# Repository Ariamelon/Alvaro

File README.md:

# Alvaro
 Pro Micro-compatible 32u4 Breakout Board

## Disclaimer
This board is a heavily-modified [Goldfish Rev. C](https://github.com/staticintlucas/Goldfish). While the schematic, basic layout, pinout (of course) etc is essentially the same, it uses 0603 components instead of 0402 and has some other changes.

## Key Features
* Mid-mount USB-C connector using a low-profile USB C 2.0 connector.
* Pin-compatible with the original Pro Micro.
* 5 extra pins on the bottom like the Elite-C and Goldfish.
* Exposed USB data lines on 2.54mm grid.
* Easier to solder than the Goldfish.
* Has fuse unlike Goldfish.
* On-board power LED.
* Fully hand-solderable.

## Changelog
* 27/09/2020: Initial commit.
* 29/09/2020: Switched D1 size from SOD323 to SOD123.
* 13/10/2020: Updated to V1.1. Added F1 1206 500mA polyfuse.
* 17/10/2020: Updated to V1.2. Moved location of parts closer to center.
* 31/10/2020: Updated to V1.3. Added 0603 power indicator LED, changed R6 from 10k to 1k LED resistor.
* 29/11/2020: Updated to V1.4. Increased size of 3225 crystal pads, changed USB C THT holes back to single oval shape, added THT pad under 32u4 to allow for the entire thing to be hand-soldered easier.
* 3/12/2020: Updated to V1.5. Decreased size of 3225 crystal pads again and changed them to THT. Staggered components to allow for easier soldering.

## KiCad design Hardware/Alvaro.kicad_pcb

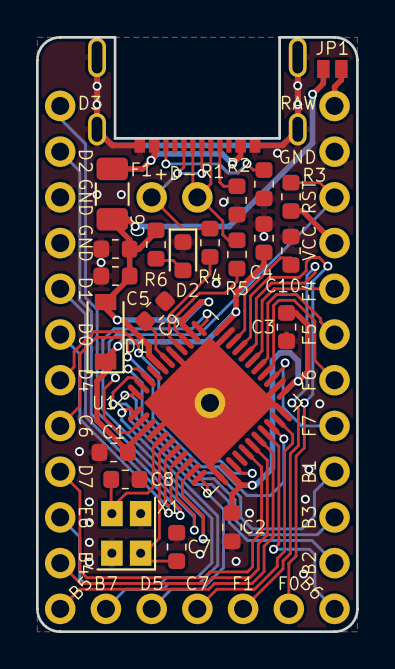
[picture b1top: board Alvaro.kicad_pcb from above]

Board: 2 copper layers, 17.8 x 33.0 mm, 27 parts (0 on the bottom side), 40 nets.

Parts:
C1, C2, C3, C4, C5, C10: 0u1; C_0603_1608Metric
C6: 4u7; C_0603_1608Metric
C7, C8: 22p; C_0603_1608Metric
C9: 1u; C_0603_1608Metric
D1: D_Schottky; D_SOD-123
D2: LED; LED_0603_1608Metric
F1: Polyfuse_Small; Fuse_1206_3216Metric
J2: 01x02; Pins2
J3, J4: 01x12; Pins12
J5: 01x05; Pins5
JP1: RAW; SolderJumper-2_P1.3mm_Open_Pad1.0x1.5mm
P1: USB_C_Receptacle_USB2.0; USB-C-C168688
R1, R2: 5k1; R_0603_1608Metric
R3: 10k; R_0603_1608Metric
R4, R5: 22; R_0603_1608Metric
R6: 1k; R_0603_1608Metric
U1: ATmega32U4; QFN-44-1EP_7x7mm_P0.5mm_EP5.2x5.2mm
X1: 16MHz; Crystal_SMD_SeikoEpson_FA238-4Pin_3.2x2.5mm

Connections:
/D+: J2.1, P1.A6, P1.B6, R4.2
/D-: J2.2, P1.A7, P1.B7, R5.2
/PB1: J3.9, U1.9
/PB2: J3.11, U1.10
/PB3: J3.10, U1.11
/PB4: J4.2, U1.28
/PB5: J4.1, U1.29
/PB6: J3.12, U1.30
/PB7: J5.5, U1.12
/PC6: J4.5, U1.31
/PC7: J5.3, U1.32
/PD0: J4.7, U1.18
/PD1: J4.8, U1.19
/PD2: J4.11, U1.20
/PD3: J4.12, U1.21
/PD4: J4.6, U1.25
/PD5: J5.4, U1.22
/PD7: J4.4, U1.27
/PE6: J4.3, U1.1
/PF0: J5.1, U1.41
/PF1: J5.2, U1.40
/PF4: J3.5, U1.39
/PF5: J3.6, U1.38
/PF6: J3.7, U1.37
/PF7: J3.8, U1.36
/RESET: J3.3, R3.1, U1.13
GND: C1.2, C2.2, C3.2, C4.2, C5.2, C6.2, C7.2, C8.2, C9.2, C10.2, D2.1, J3.2, J4.9, J4.10, P1.A1, P1.S1, R1.1, R2.1, U1.5, U1.15, U1.23, U1.33, U1.35, U1.43, U1.45, X1.2, X1.4
unnamed: C7.1, U1.17, X1.1
unnamed: C8.1, U1.16, X1.3
unnamed: C9.1, U1.6
unnamed: C10.1, U1.42
unnamed: D2.2, R6.1
unnamed: F1.2, P1.A4
unnamed: J3.1, JP1.2
unnamed: P1.A5, R1.2
unnamed: P1.B5, R2.2
unnamed: R4.1, U1.4
unnamed: R5.1, U1.3
VBUS: C5.1, C6.1, D1.2, F1.1, JP1.1, R6.2, U1.2, U1.7
VCC: C1.1, C2.1, C3.1, C4.1, D1.1, J3.4, R3.2, U1.14, U1.24, U1.34, U1.44

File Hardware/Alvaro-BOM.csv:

Name,Component,Package,Value,Qty
"C1-C5, C10",Capacitor,0603,100nF,6
C6,Capacitor,0603,4.7uF,1
"C7, C8",Capacitor,0603,22pF,2
C9,Capacitor,0603,1uF,1
D1,Schottky,SOD-123,<.5VF,1
D2,LED,0603,Any colour,1
F1,Polyfuse,1206,500mA,1
P1,USB C Female,C168688,,1
"R1, R2",Resistor,0603,5.1k,2
R3,Resistor,0603,10k,1
"R4, R5",Resistor,0603,22R,2
"R6",Resistor,0603,1k,1
U1,Atmega32U4-MU(R),QFN,-,1
X1,Crystal,3225,16MHz,1

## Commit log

2020-09-27 First upload
2020-09-28 Added Gerber files
2020-09-28 Added BOM
2020-09-29 SOD323 schottky switched to SOD123
    Bigger means less heat issues
2020-09-30 Create LICENSE
2020-10-01 Added renders and updated readme
2020-10-01 Fixed broken link oops
2020-10-01 Removed back render
2020-10-13 Updated to V1.1
    Added 1206 500mA polyfuse to design, rerouted and moved parts, changed renders
2020-10-13 Fixed BOM
2020-10-17 Added photograph
2020-10-17 Added photo of Alvaro
2020-10-17 Fixed minor typo
2020-10-17 Updated to 1.2
    Fixed/changed silkscreen, moved parts closer to center for better compatibility with pin headers
2020-10-24 Changed location of images, changed silk a bit
2020-10-24 Updated render
2020-10-31 Updated to 1.3
    Added 0603 power indicator LED, changed R6 from 10k to 1k LED resistor.
2020-10-31 Updated to V1.3
2020-11-12 Fixed error
2020-11-29 Added THT pad under the 32u4.
2020-11-29 Revert "Added THT pad under the 32u4."
    This reverts commit 5261bc7efe342fde01f2eec8e41c6f0668064f92.
2020-11-29 Updated to V1.4
2020-11-29 Revert "Updated to V1.4"
    This reverts commit e48bf29cd350433ef86578d4037b38624ab9400b.
2020-11-29 Updated to V1.4.
2020-11-29 Slightly modified polyfuse spec
2020-12-03 Updated to V1.5
